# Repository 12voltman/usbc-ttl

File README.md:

# usbc-ttl
USB-C to TTL serial adapters with male and female connector options

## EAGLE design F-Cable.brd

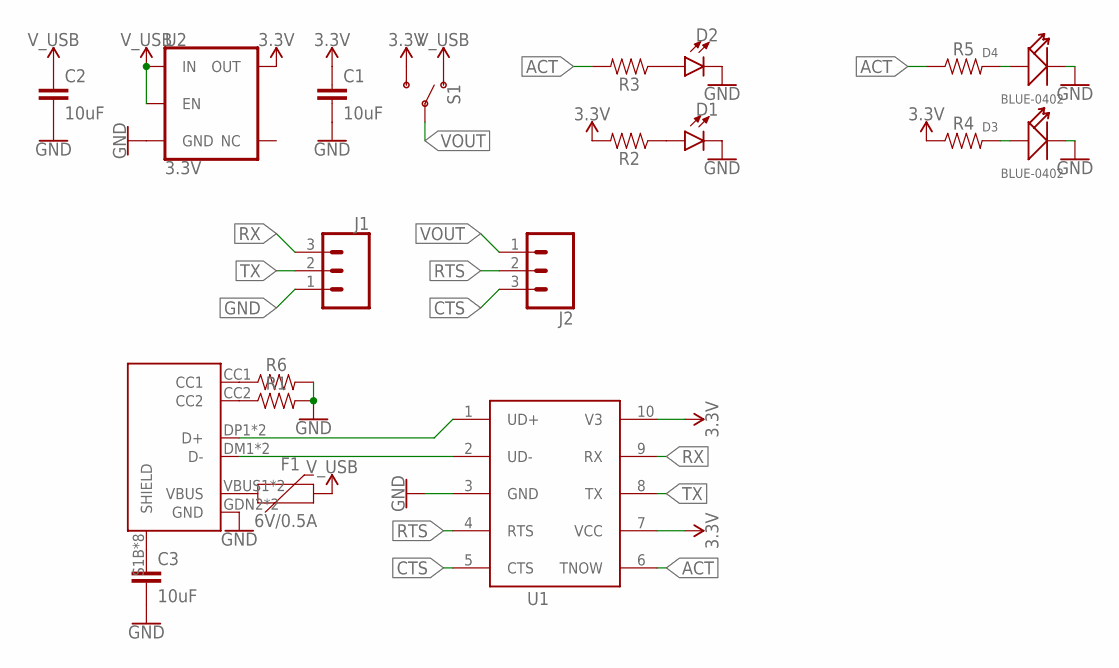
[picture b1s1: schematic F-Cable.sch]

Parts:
C1, C2, C3: 10uF; 0603
D1, D2: LED0603; LED-0603
D3, D4: BLUE-0402; LED-0402
F1: 6V/0.5A; 1206
J1, J2: CONN_03SMD_RA_MALE; 1X03_SMD_RA_MALE
R1, R2, R3, R6: 0603
R4, R5: 0402
S1: SWITCH-SPDT-SMD-RIGHT-ANGLE; SWITCH_SPST_SMD_A
U1: CH340ESMD; MSOP10
U2: 3.3V; SOT23-5
U$1: USB-C_USB2ONLY-HORZ_F; USB-C_12PIN_HORZ-F

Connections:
3.3V: C1.1, R2.2, R4.1, S1.3 (S), U1.7 (VCC), U1.10 (V3), U2.5 (OUT)
ACT: R3.2, R5.1, U1.6 (TNOW)
CTS: J2.3, U1.5 (CTS)
DM: U1.2 (UD-), U$1.DM1 (D-), U$1.DM2 (D-)
DP: U1.1 (UD+), U$1.DP1 (D+), U$1.DP2 (D+)
GND: C1.2, C2.2, C3.2, D1.C, D2.C, D3.-, D4.-, J1.1, R1.2, R6.2, U1.3 (GND), U2.2 (GND), U$1.GDN2 (GND), U$1.GND1 (GND)
unnamed: D1.A, R2.1
unnamed: D2.A, R3.1
unnamed: D4.+, R5.2
unnamed: D3.+, R4.2
unnamed: R6.1, U$1.CC1
unnamed: R1.1, U$1.CC2
RTS: J2.2, U1.4 (RTS)
RX: J1.3, U1.9 (RX)
SHIELD: C3.1, U$1.S1B (SHIELD), U$1.S1T (SHIELD), U$1.S2B (SHIELD), U$1.S2T (SHIELD), U$1.S3B (SHIELD), U$1.S3T (SHIELD), U$1.S4B (SHIELD), U$1.S4T (SHIELD)
TX: J1.2, U1.8 (TX)
VOUT: J2.1, S1.2
VUSB: F1.1, U$1.VBUS1 (VBUS), U$1.VBUS2 (VBUS)
V_USB: C2.1, F1.2, S1.1 (O), U2.1 (IN), U2.3 (EN)

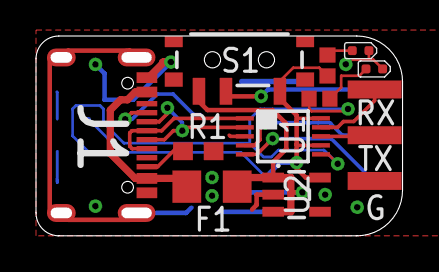
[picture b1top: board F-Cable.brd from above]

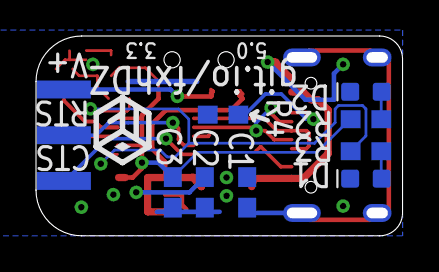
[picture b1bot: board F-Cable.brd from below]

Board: 2 copper layers, 19.8 x 10.5 mm, 20 parts (9 on the bottom side), 19 nets.

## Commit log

2019-07-16 Added second CC resistor

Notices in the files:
parts and their libraries:
SparkFun-Capacitors: Licensing: Creative Commons ShareAlike 4.0 International - https://creativecommons.org/licenses/by-sa/4.0
